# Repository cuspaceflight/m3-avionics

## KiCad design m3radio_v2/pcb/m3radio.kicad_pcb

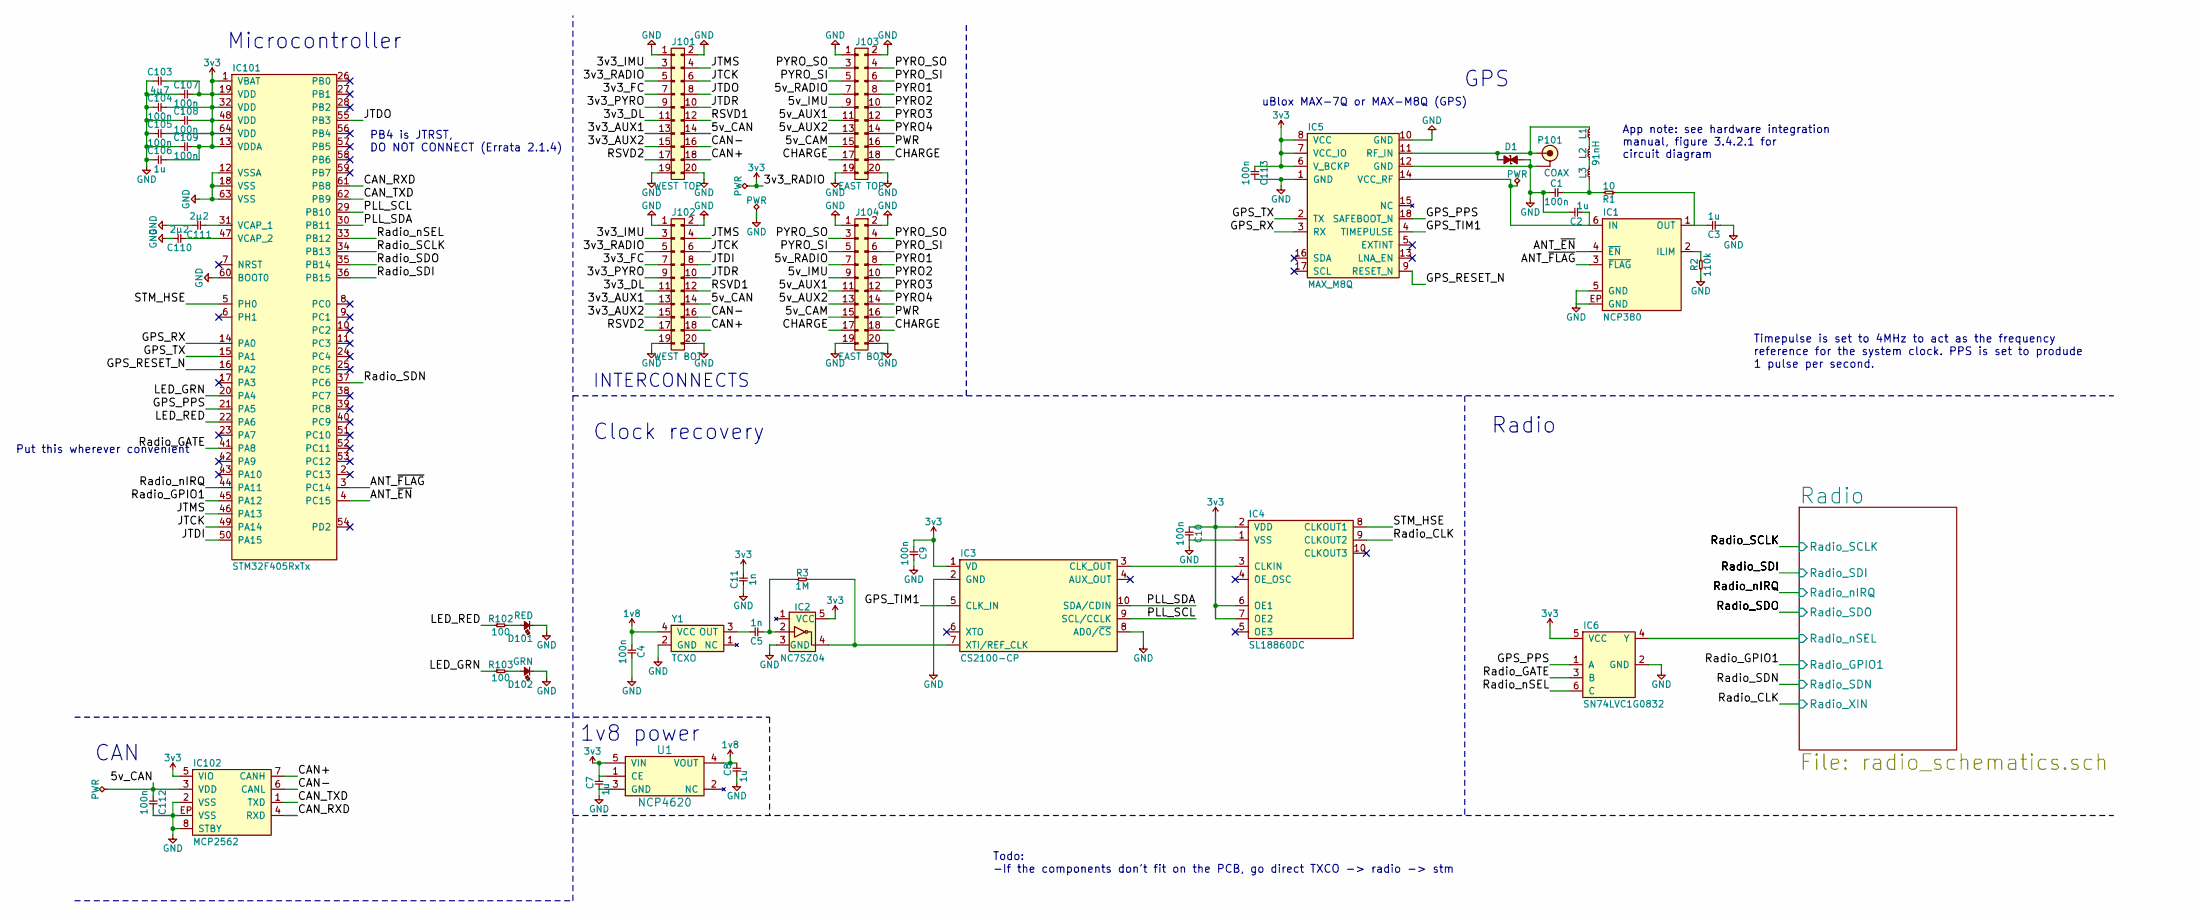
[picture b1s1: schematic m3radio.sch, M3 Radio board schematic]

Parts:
C1, C4, C9, C10, C104, C105, C107, C108, C109, C112, C113: 100n; 0402; Farnell 2496771
C2, C3, C7, C8, C106: 1u; 0402; Farnell 2496814
C5, C11: 1n; 0402; Farnell 2495166
C103: 4µ7; 0402; Farnell 2426952
C110, C111: 2µ2; 0402; Farnell 2362088
D1: ESD_DIODE; 0402; Farnell 2368169
D101: RED; 0603-LED; Farnell 2314404
D102: GRN; 0603-LED; Farnell 2290363
IC1: NCP380; DFN-6-EP-ONSEMI; Farnell 2464412
IC2: NC7SZ04; SOT-23-5; Farnell 1417667
IC3: CS2100-CP; MSOP-10; Mouser 777-CS2100CP-CZZ
IC4: SL18860DC; DFN-10-SL18860DC; Mouser 634-SL18860DC
IC5: MAX_M8Q; MAX-M8Q
IC6: SN74LVC1G0832; SC-70-6; Farnell 2406965
IC101: STM32F405RxTx; LQFP-64; Farnell 2064363
IC102: MCP2562; DFN-8-EP-MICROCHIP; Farnell 2448755
J101: WEST TOP; TFML-110-02-L-D
J102: WEST BOT; SFML-110-02-L-D-LC
J103: EAST TOP; TFML-110-02-L-D
J104: EAST BOT; SFML-110-02-L-D-LC
L1, L2, L3: 91nH; 0402-L; Farnell 2470339
P101: COAX; U.FL-R-SMT-1; Farnell 3908021
R1: 10; 0603; Farnell 1738878
R2: 110k; 0402; Farnell 2502502
R3: 1M; 0402; Farnell 2502805
R102, R103: 100; 0402; Farnell 9239111
U1: NCP4620; SC-70-5; Farnell 2464259
Y1: TCXO; TG-5006CG; Farnell 2405785

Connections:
1v8: C4.1, C8.2, U1.4 (VOUT), Y1.4 (VCC)
3v3: C7.2, C9.1, C10.1, C11.2, C103.2, C104.2, C105.2, C106.2, C107.2, C108.2, C109.2, C113.1, IC2.5 (VCC), IC3.1 (VD), IC4.2 (VDD), IC4.6 (OE1), IC4.7 (OE2), IC5.6 (V_BCKP), IC5.7 (VCC_IO), IC5.8 (VCC), IC6.5 (VCC), IC101.1 (VBAT), IC101.13 (VDDA), IC101.19 (VDD), IC101.32 (VDD), IC101.48 (VDD), IC101.64 (VDD), IC102.5 (VIO), J101.5, J102.5, U1.1 (CE), U1.5 (VIN); also elsewhere on the board
/3v3_AUX1: J101.13, J102.13
/3v3_AUX2: J101.15, J102.15
/3v3_DL: J101.11, J102.11
/3v3_FC: J101.7, J102.7
/3v3_IMU: J101.3, J102.3
/3v3_PYRO: J101.9, J102.9
/5v_AUX1: J103.11, J104.11
/5v_AUX2: J103.13, J104.13
/5v_CAM: J103.15, J104.15
/5v_CAN: C112.1, IC102.3 (VDD), J101.14, J102.14
/5v_IMU: J103.9, J104.9
/5v_RADIO: J103.7, J104.7
/ANT_~EN: IC1.4 (~EN), IC101.4 (PC15)
/ANT_~FLAG: IC1.3 (~FLAG), IC101.3 (PC14)
/CAN+: IC102.7 (CANH), J101.18, J102.18
/CAN-: IC102.6 (CANL), J101.16, J102.16
/CAN_RXD: IC101.61 (PB8), IC102.4 (RXD)
/CAN_TXD: IC101.62 (PB9), IC102.1 (TXD)
/CHARGE: J103.17, J103.18, J104.17, J104.18
/GPS_PPS: IC5.18 (SAFEBOOT_N), IC6.1 (A), IC101.21 (PA5)
/GPS_RESET_N: IC5.9 (RESET_N), IC101.16 (PA2)
/GPS_RX: IC5.3 (RX), IC101.14 (PA0)
/GPS_TIM1: IC3.5 (CLK_IN), IC5.4 (TIMEPULSE)
/GPS_TX: IC5.2 (TX), IC101.15 (PA1)
/JTCK: IC101.49 (PA14), J101.6, J102.6
/JTDI: IC101.50 (PA15), J102.8
/JTDO: IC101.55 (PB3), J101.8
/JTDR: J101.10, J102.10
/JTMS: IC101.46 (PA13), J101.4, J102.4
/LED_GRN: IC101.20 (PA4), R103.1
/LED_RED: IC101.22 (PA6), R102.1
/PLL_SCL: IC3.9 (SCL/CCLK), IC101.29 (PB10)
/PLL_SDA: IC3.10 (SDA/CDIN), IC101.30 (PB11)
/PWR: J103.16, J104.16
/PYRO1: J103.8, J104.8
/PYRO2: J103.10, J104.10
/PYRO3: J103.12, J104.12
/PYRO4: J103.14, J104.14
/PYRO_SI: J103.5, J103.6, J104.5, J104.6
/PYRO_SO: J103.3, J103.4, J104.3, J104.4
/RSVD1: J101.12, J102.12
/RSVD2: J101.17, J102.17
/Radio/Radio_nSEL: IC6.4 (Y); also elsewhere on the board
/Radio_CLK: IC4.9 (CLKOUT2); also elsewhere on the board
/Radio_GATE: IC6.3 (B), IC101.41 (PA8)
/Radio_GPIO1: IC101.45 (PA12); also elsewhere on the board
/Radio_SCLK: IC101.34 (PB13); also elsewhere on the board
/Radio_SDI: IC101.36 (PB15); also elsewhere on the board
/Radio_SDN: IC101.37 (PC6); also elsewhere on the board
/Radio_SDO: IC101.35 (PB14); also elsewhere on the board
/Radio_nIRQ: IC101.44 (PA11); also elsewhere on the board
/STM_HSE: IC4.8 (CLKOUT1), IC101.5 (PH0)
GND: C1.1, C2.2, C3.1, C4.2, C7.1, C8.1, C9.2, C10.2, C11.1, C103.1, C104.1, C105.1, C106.1, C107.1, C108.1, C109.1, C110.2, C111.2, C112.2, C113.2, D1.2, D101.1, D102.1, IC1.5 (GND), IC1.EP (GND), IC2.3 (GND), IC3.2 (GND), IC3.8 (AD0/~CS), IC4.1 (VSS), IC5.1 (GND), IC5.10 (GND), IC5.12 (GND), IC6.2 (GND), IC101.12 (VSSA), IC101.18 (VSS), IC101.60 (BOOT0), IC101.63 (VSS), IC102.2 (VSS), IC102.8 (STBY), IC102.EP (VSS), J101.1, J101.2, J101.19, J101.20, J102.1, J102.2, J102.19, J102.20, J103.1, J103.2, J103.19, J103.20, J104.1, J104.2, J104.19, J104.20, P101.2 (GND), R2.1, U1.3 (GND), Y1.2 (GND); also elsewhere on the board
unnamed: C1.2, L3.1, R1.2
unnamed: C2.1, IC1.6 (IN), IC5.14 (VCC_RF)
unnamed: C3.2, IC1.1 (OUT), R1.1
unnamed: C5.1, IC2.2, R3.1
unnamed: C5.2, Y1.3 (OUT)
unnamed: C110.1, IC101.47 (VCAP_2)
unnamed: C111.1, IC101.31 (VCAP_1)
unnamed: D1.1, IC5.11 (RF_IN), L1.2, P101.1 (RF)
unnamed: D101.2, R102.2
unnamed: D102.2, R103.2
unnamed: IC1.2 (ILIM), R2.2
unnamed: IC2.4, IC3.7 (XTI/REF_CLK), R3.2
unnamed: IC3.3 (CLK_OUT), IC4.3 (CLKIN)
unnamed: L1.1, L2.2
unnamed: L2.1, L3.2

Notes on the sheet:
CAN
Microcontroller
Radio
GPS
uBlox MAX-7Q or MAX-M8Q (GPS)
INTERCONNECTS
PB4 is JTRST, DO NOT CONNECT (Errata 2.1.4)
App note: see hardware integration manual, figure 3.4.2.1 for circuit diagram
1v8 power
Clock recovery
Todo: -If the components don't fit on the PCB, go direct TXCO -> radio -> stm
Put this wherever convenient
Timepulse is set to 4MHz to act as the frequency reference for the system clock. PPS is set to produde 1 pulse per second.

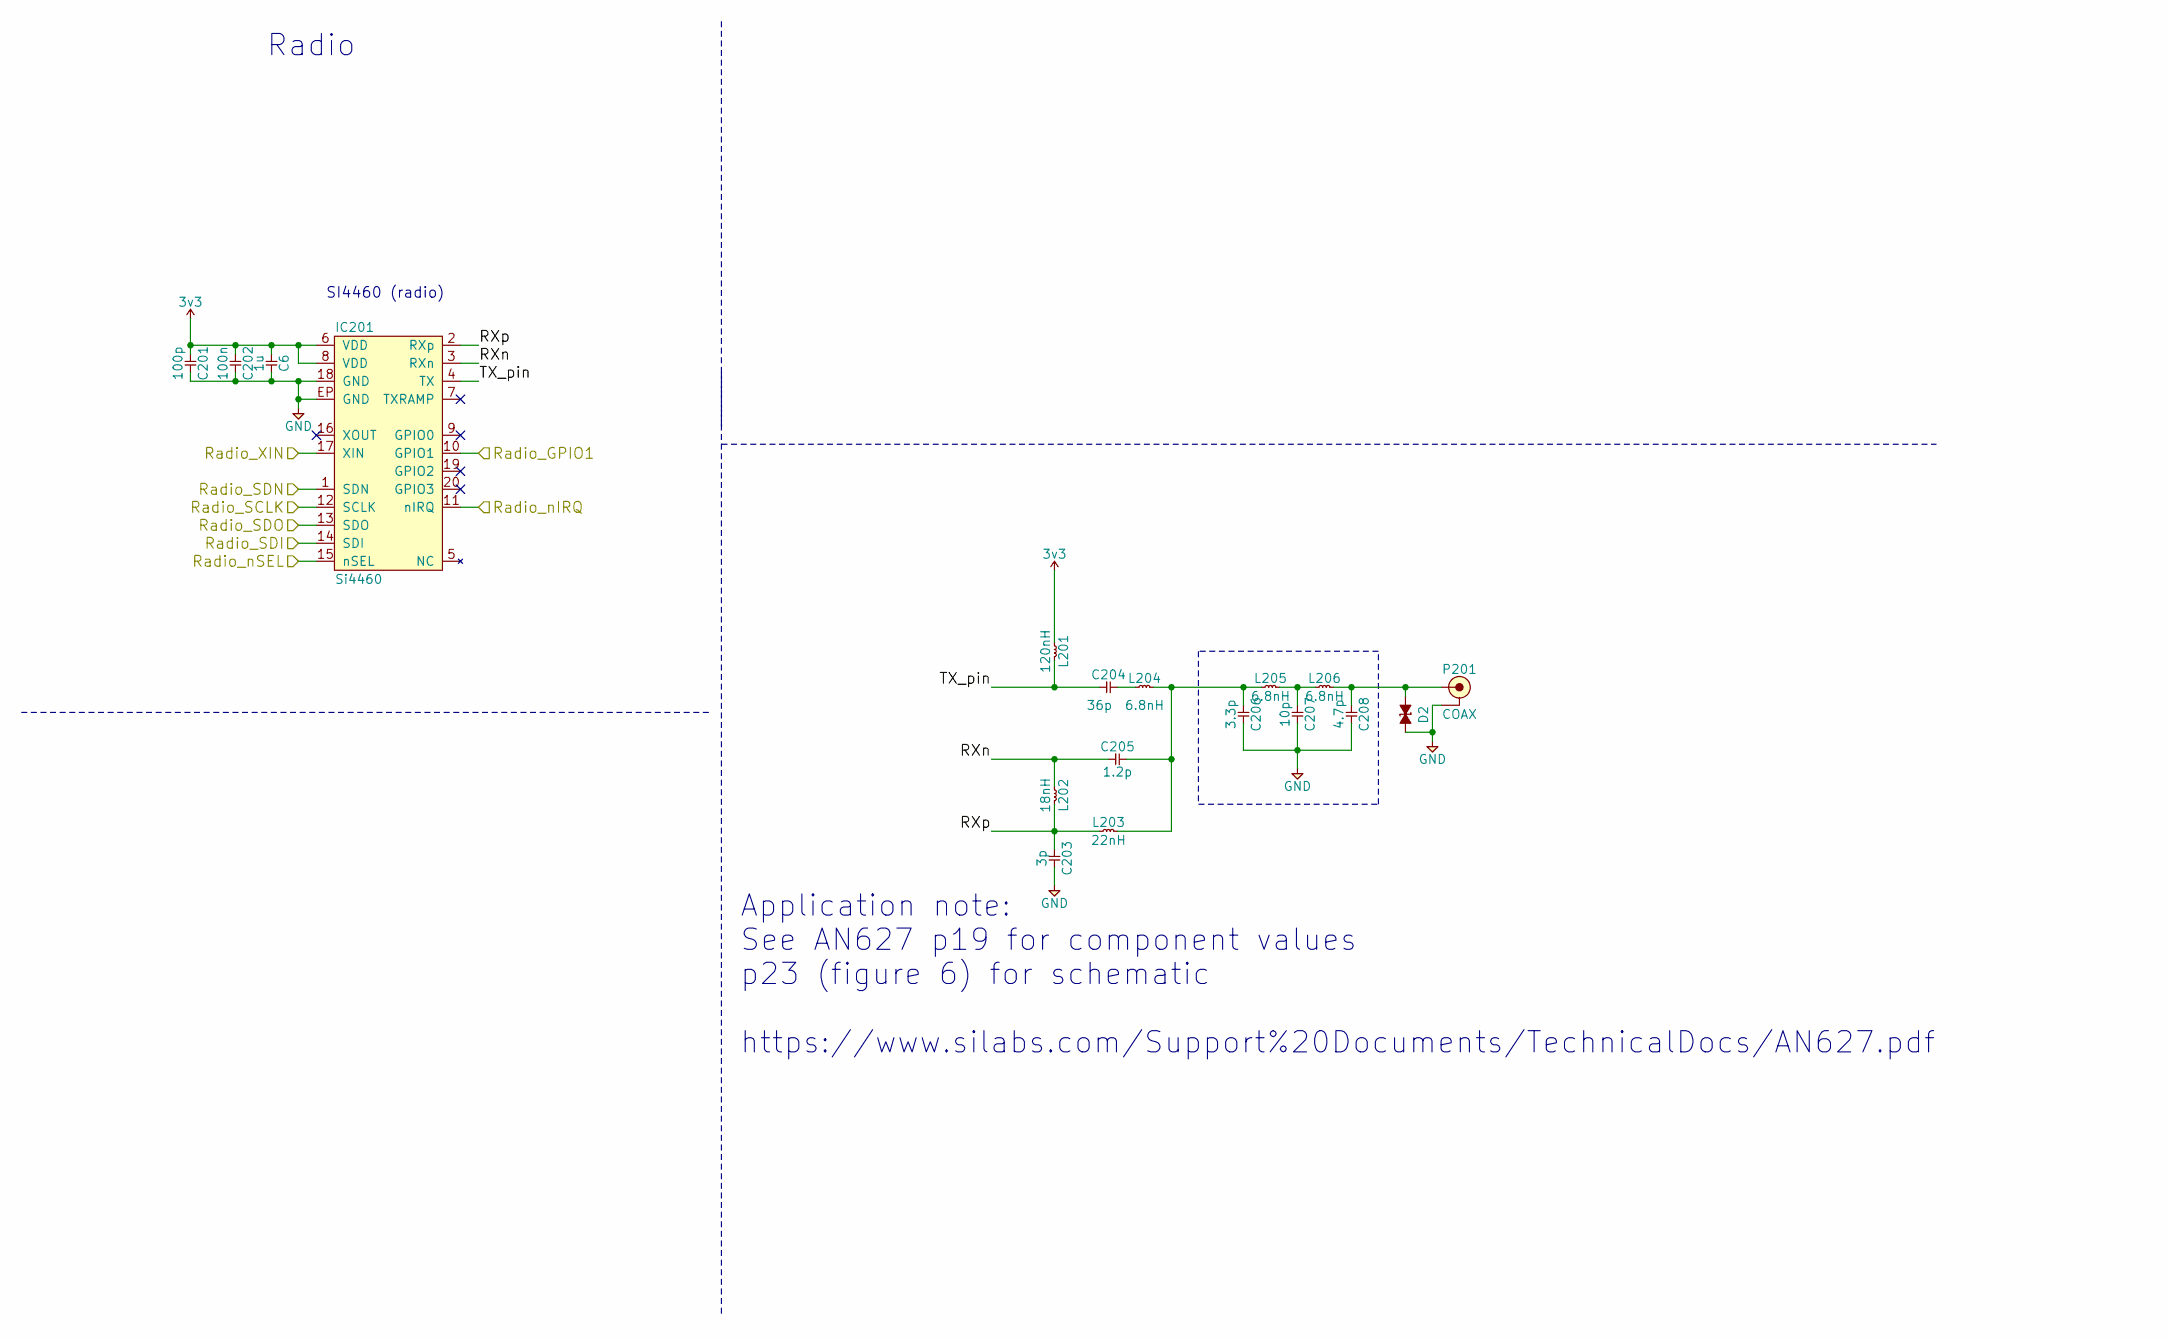
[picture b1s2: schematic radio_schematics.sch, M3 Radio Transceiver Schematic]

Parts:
C6: 1u; 0402; Farnell 2496814
C201: 100p; 0402; Farnell 2496792
C202: 100n; 0402; Farnell 2496771
C203: 3p; 0402; Farnell 2210752
C204: 36p; 0402; Farnell 1865427
C205: 1.2p; 0402; Farnell 2218843
C206: 3.3p; 0402; Farnell 2434610
C207: 10p; 0402; Farnell 2496790
C208: 4.7p; 0402; Farnell 2434644
D2: ESD_DIODE; 0402; Farnell 2368169
IC201: Si4460; QFN-20-EP-SI; Farnell 2462635
L201: 120nH; 0603-L; Farnell 1865812
L202: 18nH; 0603-L; Farnell 2424720
L203: 22nH; 0603-L; Farnell 1711755
L204, L205, L206: 6.8nH; 0603-L; Farnell 1515395
P201: COAX; U.FL-R-SMT-1; Farnell 3908021

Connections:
3v3: C6.1, C201.1, C202.1, IC201.6 (VDD), IC201.8 (VDD), L201.1; also elsewhere on the board
/Radio/RXn: C205.1, IC201.3 (RXn), L202.1
/Radio/RXp: C203.1, IC201.2 (RXp), L202.2, L203.1
/Radio/Radio_nSEL: IC201.15 (nSEL); also elsewhere on the board
/Radio/TX_pin: C204.1, IC201.4 (TX), L201.2
/Radio_CLK: IC201.17 (XIN); also elsewhere on the board
/Radio_GPIO1: IC201.10 (GPIO1); also elsewhere on the board
/Radio_SCLK: IC201.12 (SCLK); also elsewhere on the board
/Radio_SDI: IC201.14 (SDI); also elsewhere on the board
/Radio_SDN: IC201.1 (SDN); also elsewhere on the board
/Radio_SDO: IC201.13 (SDO); also elsewhere on the board
/Radio_nIRQ: IC201.11 (nIRQ); also elsewhere on the board
GND: C6.2, C201.2, C202.2, C203.2, C206.2, C207.2, C208.2, D2.2, IC201.18 (GND), IC201.EP (GND), P201.2 (GND); also elsewhere on the board
unnamed: C204.2, L204.1
unnamed: C205.2, C206.1, L203.2, L204.2, L205.1
unnamed: C207.1, L205.2, L206.1
unnamed: C208.1, D2.1, L206.2, P201.1 (RF)

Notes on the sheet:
SI4460 (radio)
Radio
Application note: See AN627 p19 for component values p23 (figure 6) for schematic https://www.silabs.com/Support%20Documents/TechnicalDocs/AN627.pdf

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
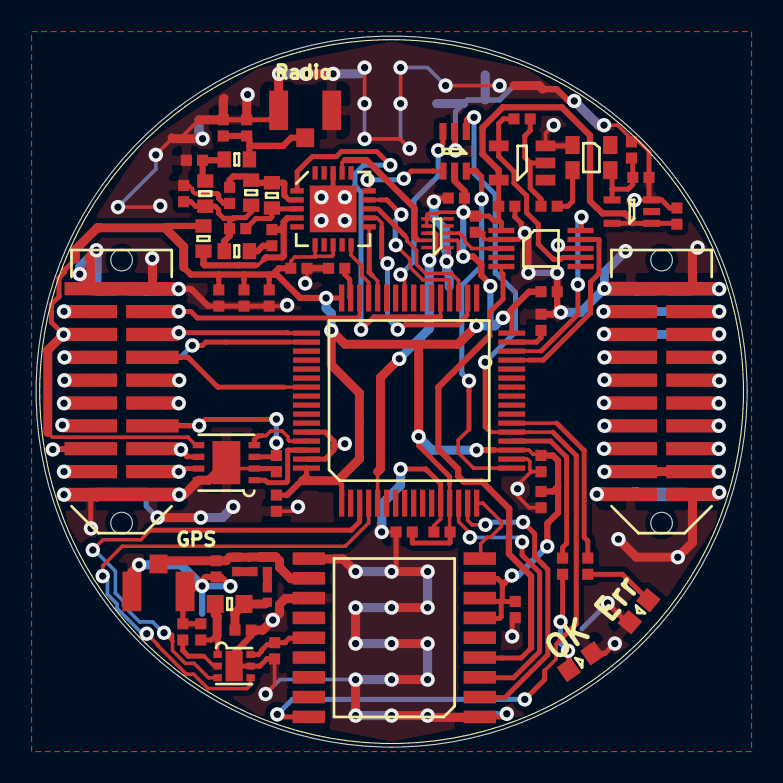
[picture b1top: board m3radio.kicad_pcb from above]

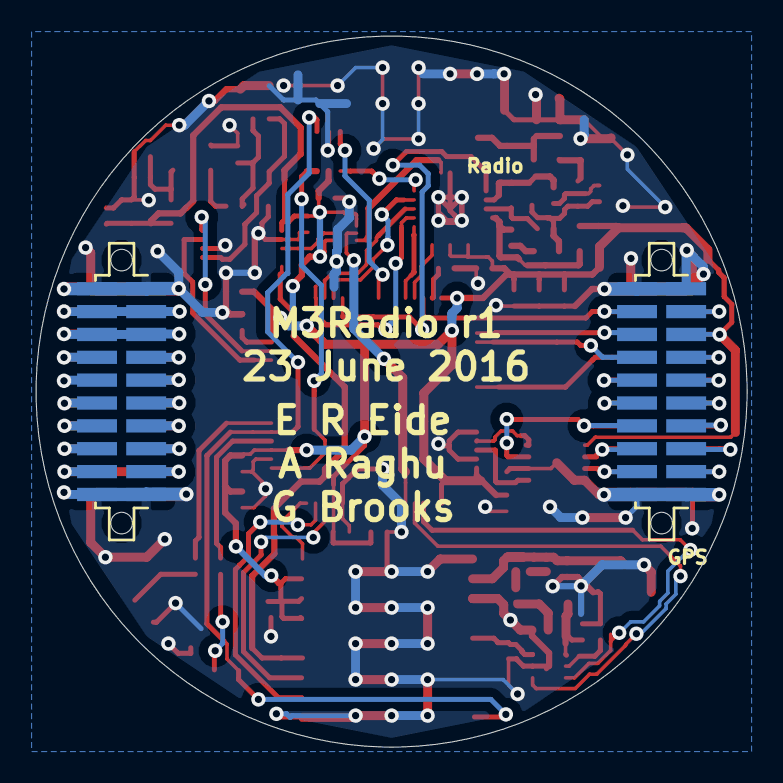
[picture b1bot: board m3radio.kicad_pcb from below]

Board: 2 copper layers, 39.5 x 39.5 mm, 65 parts (2 on the bottom side), 78 nets.
